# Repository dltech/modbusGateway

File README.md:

# modbusGateway
An STM32 based board with RS485, ETHERNET, USB Host and sub-GHz interfaces. I will use it for modbus TCP modbus RTU gateway.

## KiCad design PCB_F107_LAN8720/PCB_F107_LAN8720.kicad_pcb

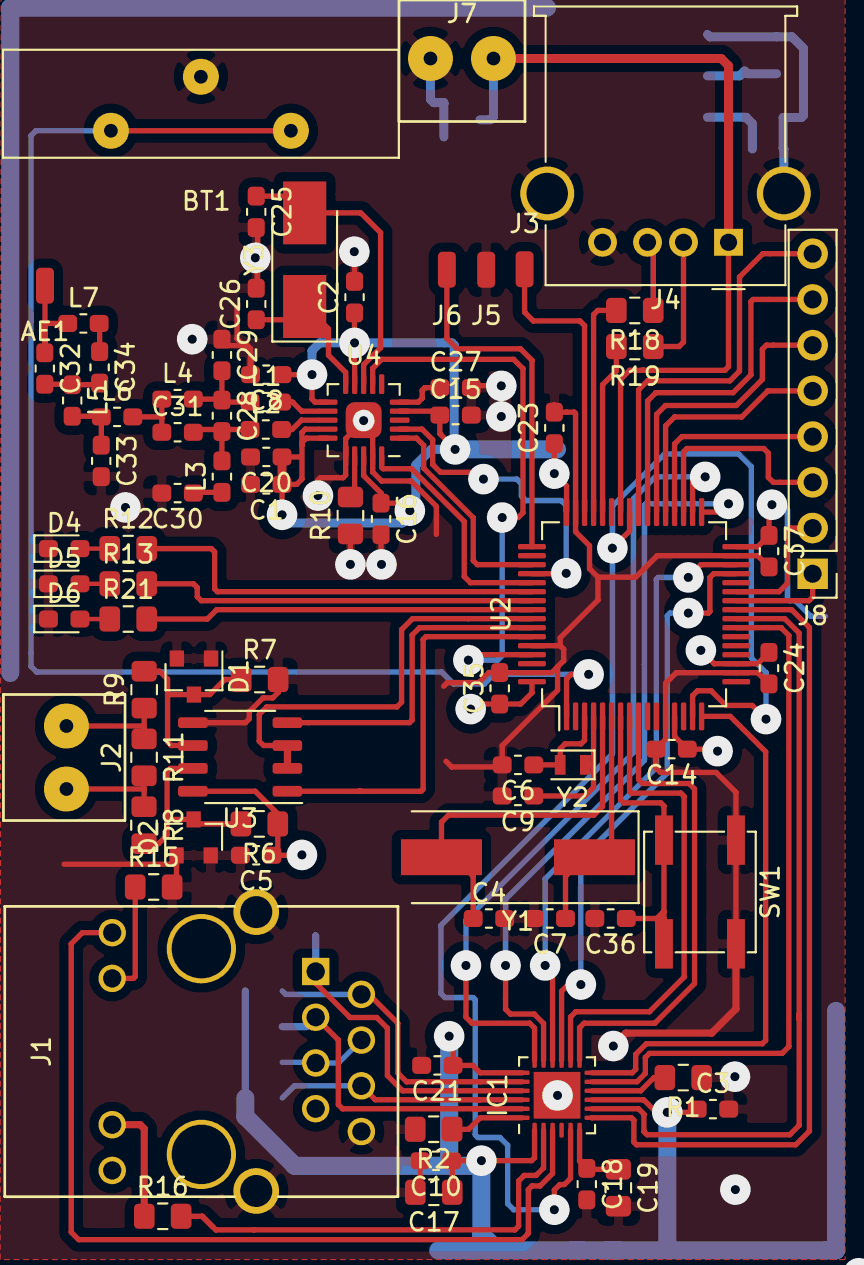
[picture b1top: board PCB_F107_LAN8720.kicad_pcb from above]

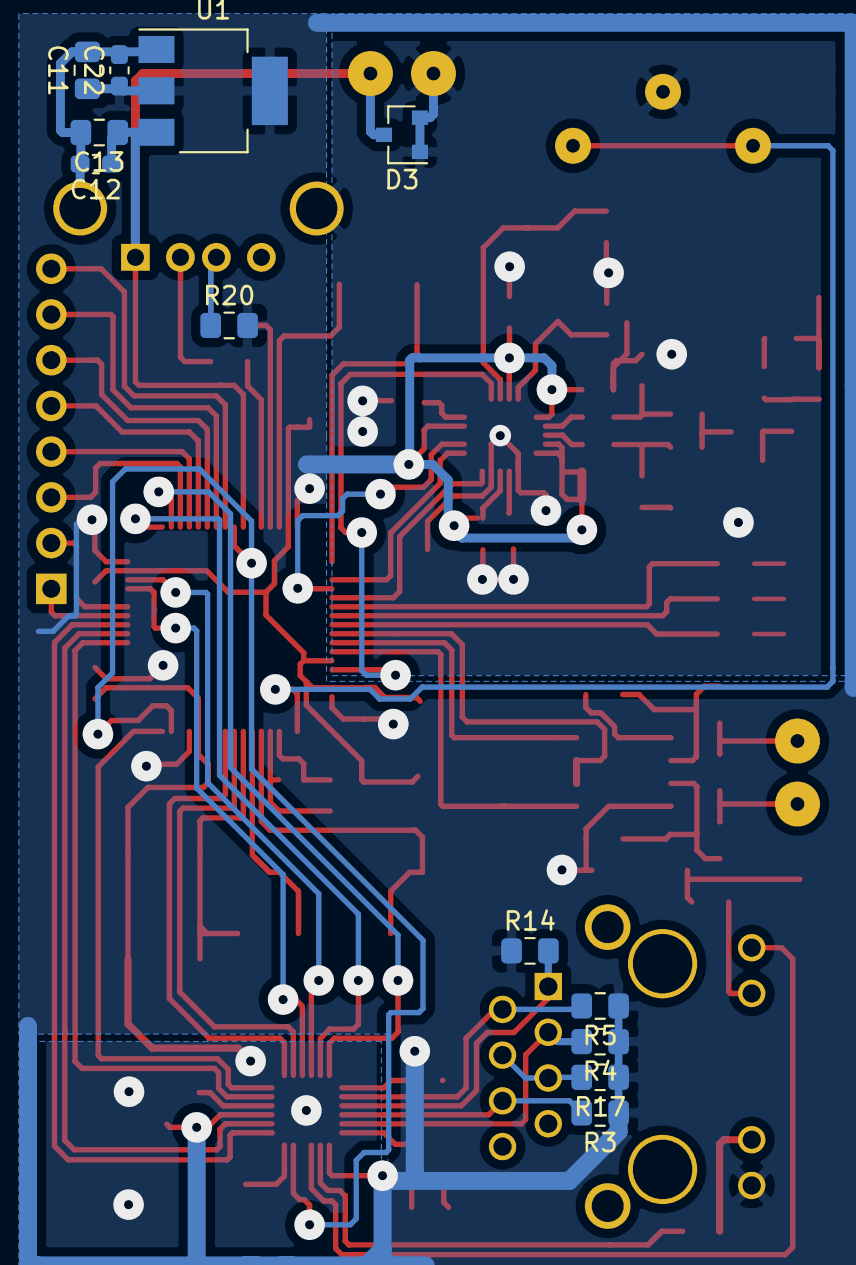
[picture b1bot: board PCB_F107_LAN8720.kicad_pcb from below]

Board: 2 copper layers, 90 parts (12 on the bottom side), 77 nets.

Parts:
AE1: Antenna; SolderWirePad_1x01_SMD_1x2mm
BT1: 3V; 2032_vertical
C1, C2, C3, C5, C8, C10, C12, C20, C21, C22, C23, C24, C35, C36, C37: 100nF; C_0603_1608Metric_Pad1.05x0.95mm_HandSolder
C4, C6, C7, C9, C25, C26, C27: 22pF; C_0603_1608Metric_Pad1.05x0.95mm_HandSolder
C11, C13, C17: 4.7uF; C_0805_2012Metric_Pad1.15x1.40mm_HandSolder
C14, C15, C16: 0.1uF; C_0603_1608Metric_Pad1.05x0.95mm_HandSolder
C18: 470pF; C_0603_1608Metric_Pad1.05x0.95mm_HandSolder
C19: 1uF; C_0805_2012Metric_Pad1.15x1.40mm_HandSolder
C28: 1pF; C_0603_1608Metric_Pad1.05x0.95mm_HandSolder
C29, C31: 1.5pF; C_0603_1608Metric_Pad1.05x0.95mm_HandSolder
C30: 100pF; C_0603_1608Metric_Pad1.05x0.95mm_HandSolder
C32: 12pF; C_0603_1608Metric_Pad1.05x0.95mm_HandSolder
C33: 3.3pF; C_0603_1608Metric_Pad1.05x0.95mm_HandSolder
C34: 47pF; C_0603_1608Metric_Pad1.05x0.95mm_HandSolder
D1, D2, D3: BZX84-C5V1; D_SOT-23_ANK
D4, D5, D6: LED; LED_0603_1608Metric_Pad1.05x0.95mm_HandSolder
IC1: LAN8720A; QFN-24-1EP_4x4mm_P0.5mm_EP2.6x2.6mm
J1: RJ45_HR911105A; HR911105A
J2: 485; KF350x2
J3, J5, J6: .; SolderWirePad_1x01_SMD_1x2mm
J4: USB_B; USB_A_Molex_67643_Horizontal
J7: Power; KF350x2
J8: DBG; PinHeader_1x08_P2.54mm_Vertical
L1, L2, L5, L6: 12nH; L_0603_1608Metric_Pad1.05x0.95mm_HandSolder
L3, L4: 18nH; L_0603_1608Metric_Pad1.05x0.95mm_HandSolder
L7: 3.3nH; L_0603_1608Metric_Pad1.05x0.95mm_HandSolder
R1, R10: 10K; R_0805_2012Metric_Pad1.15x1.40mm_HandSolder
R2: 12.1K; R_0805_2012Metric_Pad1.15x1.40mm_HandSolder
R3, R4, R5, R14: 49.9; R_0805_2012Metric_Pad1.15x1.40mm_HandSolder
R6, R7: 1k; R_0805_2012Metric_Pad1.15x1.40mm_HandSolder
R8, R9, R11, R12, R13, R21: 100; R_0805_2012Metric_Pad1.15x1.40mm_HandSolder
R15, R16: 330; R_0805_2012Metric_Pad1.15x1.40mm_HandSolder
R17: 0; R_0805_2012Metric_Pad1.15x1.40mm_HandSolder
R18, R19: 22; R_0805_2012Metric_Pad1.15x1.40mm_HandSolder
R20: 1K5; R_0805_2012Metric_Pad1.15x1.40mm_HandSolder
SW1: RESET; SW_SPST_EVQP0
U1: NCP1117ST33T3G; SOT-223-3_TabPin2
U2: STM32F107RC_Short_Name; LQFP-64_10x10mm_P0.5mm
U3: ADM3485; SOP-8_3.9x4.9mm_P1.27mm
U4: CC1101; cc1101
Y1: 25MHz; Crystal_SMD_HC49-SD
Y2: 32768; Crystal_SMD_2012-2Pin_2.0x1.2mm
Y3: 26MHz; Crystal_SMD_5032-2Pin_5.0x3.2mm_HandSoldering

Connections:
/485RST: U2.57, U3.2, U3.3
/CLK_50M: IC1.5, U2.15, U2.41
/CRS_DV: IC1.11, U2.23
/JTCK/SWCLK: J6.1, U2.49
/JTMS/SWDIO: J3.1, U2.46
/MDC: IC1.13, U2.9
/MDIO: IC1.12, U2.16
/MISO: U2.52, U4.2
/MOSI: U2.53, U4.20
/NSS: U2.61, U4.7
/PB0: J8.1, U2.26
/PB1: J8.2, U2.27
/PB14: J8.3, U2.35
/PB15: J8.4, U2.36
/PC6: J8.5, U2.37
/PC7: J8.6, U2.38
/PC8: J8.7, U2.39
/PC9: J8.8, U2.40
/PHY_nINT: IC1.14, U2.8
/PHY_nRST: IC1.15, U2.29
/RXD0: IC1.8, U2.24
/RXD1: IC1.7, U2.25
/SCK: U2.51, U4.1
/TXD0: IC1.17, U2.33
/TXD1: IC1.18, U2.34
/TXEN: IC1.16, U2.30
/UART_RX: U2.59, U3.1
/UART_TX: U2.58, U3.4
/USB_DM: R19.2, U2.44
/USB_DP: R18.2, U2.45
/VBUS: C12.1, C13.1, D3.1, J4.1, J7.1, U1.3, U2.42
/led1: R12.2, U2.54
/led2: R13.2, U2.55
/led3: R21.2, U2.56
GND: BT1.2, C1.2, C2.2, C3.2, C4.2, C5.2, C6.2, C7.2, C8.2, C9.2, C10.2, C11.2, C12.2, C13.2, C14.2, C15.2, C16.2, C17.2, C18.2, C19.2, C20.2, C21.2, C22.2, C23.2, C24.2, C25.2, C26.2, C27.2, C29.1, C30.2, C33.2, C35.2, C36.2, C37.2, D1.2, D2.2, D3.2, D4.1, D5.1, D6.1, IC1.25, J1.8, J1.13, J4.4, J4.5, J5.1, J7.2, R1.1, R2.2, R7.2, R10.1, R15.2, SW1.1, U1.1, U2.12, U2.18, U2.31, U2.47, U2.60, U2.63, U3.5, U4.16, U4.19
unnamed: AE1.1, C32.1, L7.1
unnamed: BT1.1, U2.1
unnamed: C4.1, U2.5, Y1.2
unnamed: C6.1, U2.3, Y2.2
unnamed: C7.1, U2.6, Y1.1
unnamed: C9.1, U2.4, Y2.1
unnamed: C18.1, C19.1, IC1.6
unnamed: C25.1, U4.8, Y3.2
unnamed: C26.1, U4.10, Y3.1
unnamed: C27.1, U4.5
unnamed: C28.1, C29.2, L1.1, L4.2
unnamed: C28.2, C31.2, L2.1, L3.2
unnamed: C30.1, L3.1
unnamed: C31.1, L4.1, L6.2
unnamed: C32.2, C34.2, L5.1
unnamed: C33.1, L5.2, L6.1
unnamed: C34.1, L7.2
unnamed: C36.1, SW1.2, U2.7
unnamed: D1.1, R7.1, R9.2, U3.6
unnamed: D2.1, R6.2, R8.2, U3.7
unnamed: D4.2, R12.1
unnamed: D5.2, R13.1
unnamed: D6.2, R21.1
unnamed: IC1.2, R16.2
unnamed: IC1.3, J1.GA
unnamed: IC1.10, R1.2
unnamed: IC1.20, J1.2, R5.2
unnamed: IC1.21, J1.1, R14.2
unnamed: IC1.22, J1.6, R3.2
unnamed: IC1.23, J1.3, R4.2
unnamed: IC1.24, R2.1
unnamed: J1.4, J1.5, R17.2
unnamed: J1.GK, R15.1
unnamed: J1.YK, R16.1
unnamed: J2.1, R8.1, R11.2
unnamed: J2.2, R9.1, R11.1
unnamed: J4.2, R19.1
unnamed: J4.3, R18.1, R20.1
unnamed: L1.2, U4.12
unnamed: L2.2, U4.13
unnamed: R10.2, U4.17
VCC: C1.1, C2.1, C3.1, C5.1, C8.1, C10.1, C11.1, C14.1, C15.1, C16.1, C17.1, C20.1, C21.1, C22.1, C23.1, C24.1, C35.1, C37.1, IC1.1, IC1.9, IC1.19, J1.YA, R3.1, R4.1, R5.1, R6.1, R14.1, R17.1, R20.2, U1.2, U2.13, U2.19, U2.32, U2.48, U2.64, U3.8, U4.4, U4.9, U4.11, U4.14, U4.15, U4.18

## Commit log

2020-08-17 schematic and PCB
2020-09-10 working schematic
2020-09-11 leds
2020-12-02 libraries
2021-06-17 some description
2021-08-29 documentation found
2022-06-05 my hal added
2022-06-05 eth regs
2022-06-05 removed libopencm3
2022-06-07 can regs
